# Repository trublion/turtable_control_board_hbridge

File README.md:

## Description

HW control board for turntable. Controls a DC motor with a H-bridge, reads an analog audio signal envelope, dual-PCB design.

## Links (datasheets and documentation)

[IEC plug](https://www.schurter.com/en/datasheet/typ_6765.pdf)  
[Potentiometer RK09L](https://tech.alpsalpine.com/prod/e/pdf/potentiometer/rotarypotentiometers/rk09l/rk09l.pdf)  
[Neutrik combo](https://www.neutrik.com/en/product/nj3fp6c.pdf)  
[74HCT4066](https://assets.nexperia.com/documents/data-sheet/74HC_HCT4066.pdf)  
[Shunt resistors](https://www.te.com/commerce/DocumentDelivery/DDEController?Action=showdoc&DocId=Data+Sheet%7F9-1773463-7%7FG%7Fpdf%7FEnglish%7FENG_DS_9-1773463-7_G.pdf%7FCAT-C339-A76B)  
[BAS21 small signal diode](https://www.vishay.com/docs/85540/bas19.pdf)  
[Zener diodes](https://assets.nexperia.com/documents/data-sheet/BZX84_SER.pdf)  
[Electrolytic capacitors](https://industrial.panasonic.com/cdbs/www-data/pdf/RDE0000/ABA0000C1181.pdf)  
[LM358 comparator](https://www.ti.com/lit/ds/symlink/lm158-n.pdf)  
[LM833 operational amplifier](https://www.ti.com/lit/ds/symlink/lm833-n.pdf)  
[LM2674 DCDC controller](https://www.ti.com/lit/ds/symlink/lm2674.pdf)  
[MBRS3100T3G Schottky power diode](https://www.onsemi.com/pdf/datasheet/mbrs3100t3-d.pdf)  
[RS2 power diode](https://www.semiee.com/file/ELMX/MULTICOMP-RS2A.pdf)  
[Power inductor](https://www.bourns.com/docs/Product-Datasheets/SRR0735A.pdf)

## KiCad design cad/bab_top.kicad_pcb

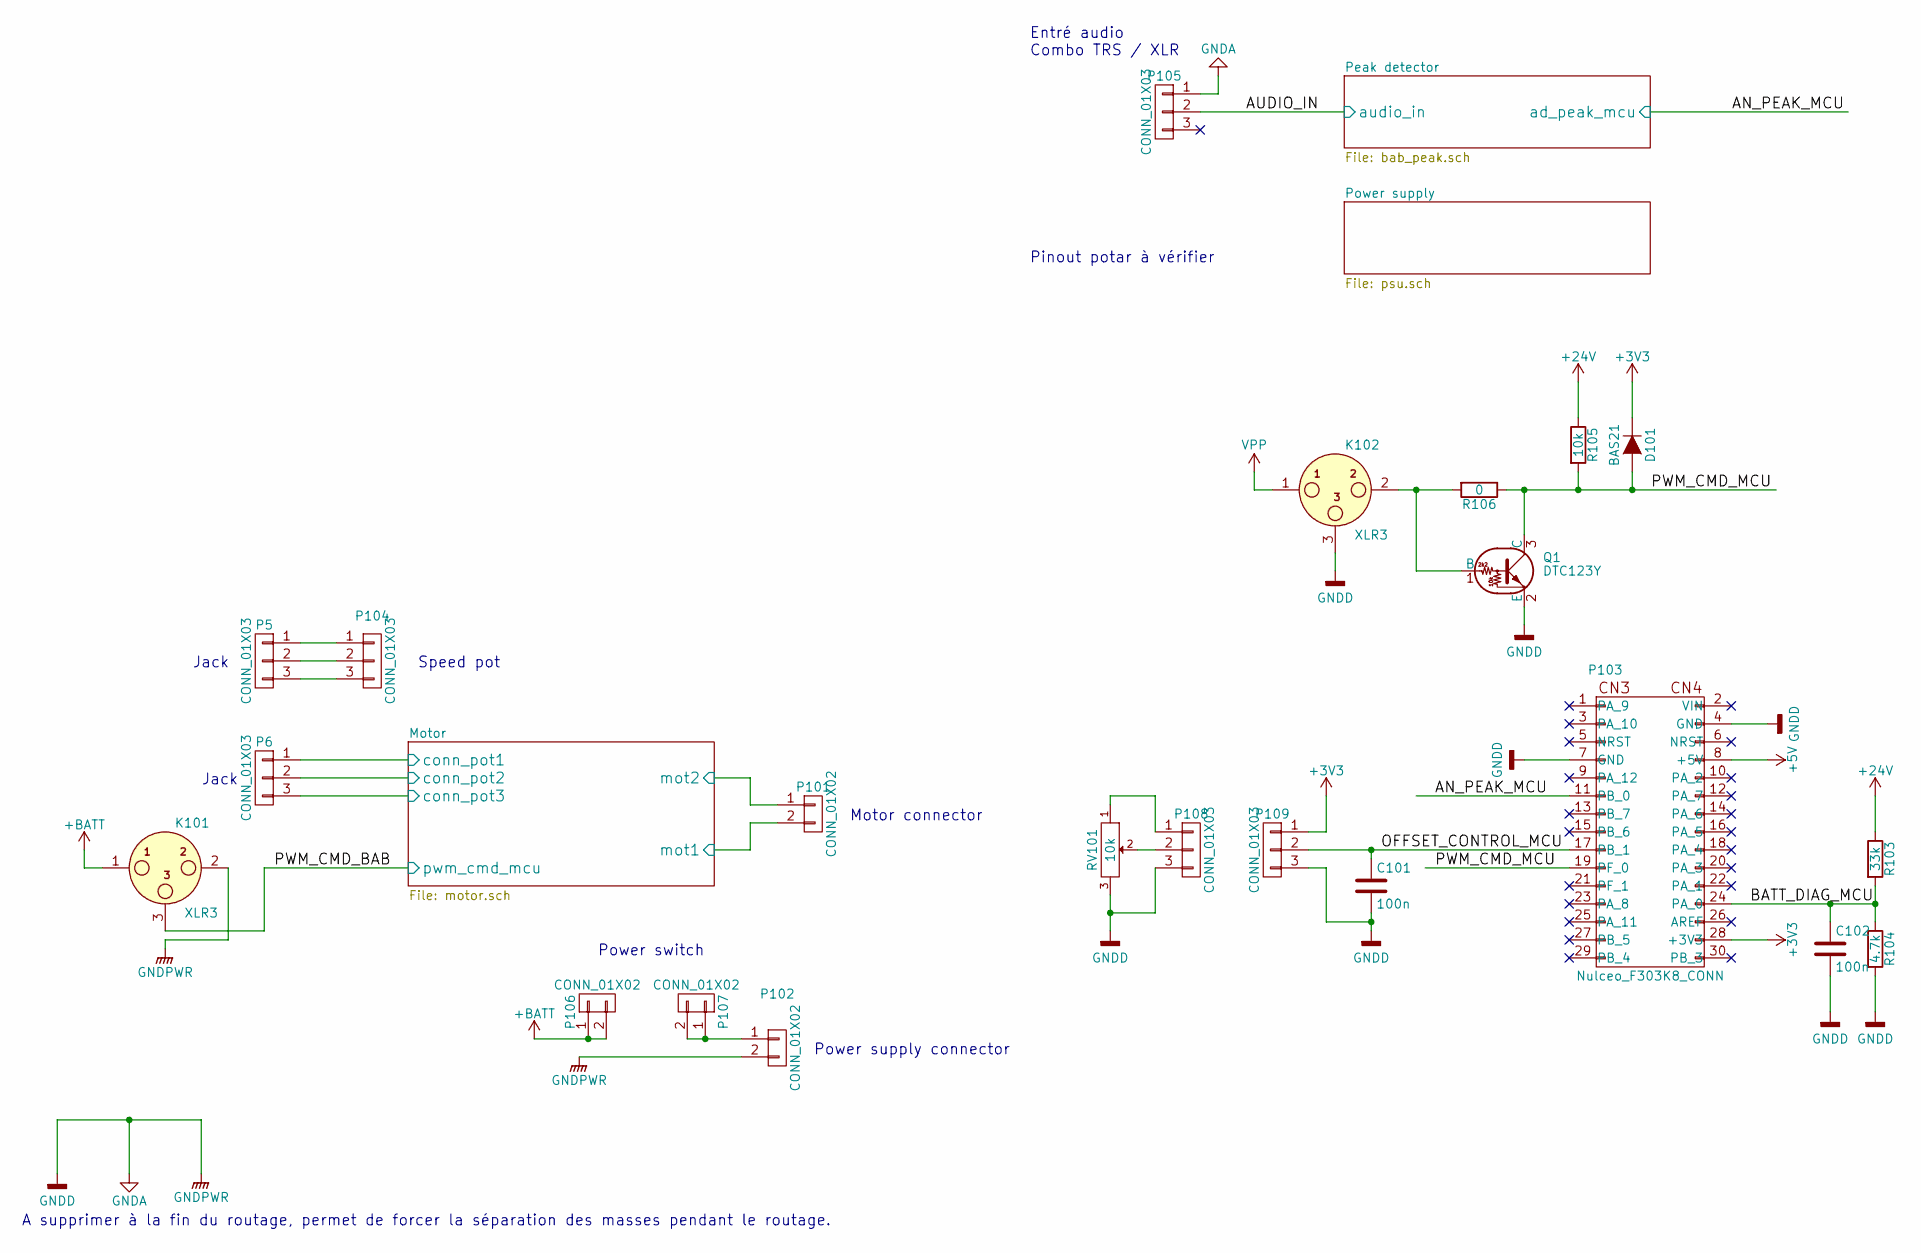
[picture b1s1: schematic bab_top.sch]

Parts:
C101, C102: 100n; C_0805_HandSoldering
D101: BAS21; SOT-23
K101, K102: XLR3; Pin_Header_Straight_1x03
P5, P6, P104, P105, P108, P109: CONN_01X03; Pin_Header_Straight_1x03
P101, P102, P106, P107: CONN_01X02; bornier2
P103: Nulceo_F303K8_CONN; Nucleo_F303K8_CONN
Q1: DTC123Y; SOT-23_Handsoldering
R103: 33k; C_0805_HandSoldering
R104: 4.7k; C_0805_HandSoldering
R105: 10k; C_0805_HandSoldering
R106: 0; C_0805_HandSoldering
RV101: 10k; Pin_Header_Straight_1x03

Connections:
+5V: P103.8 (+5V); also elsewhere on the board
+24V: R103.1, R105.1; also elsewhere on the board
+BATT: K101.1, P106.1, P106.2; also elsewhere on the board
/BATT_DIAG_MCU: C102.1, P103.24 (PA_0), R103.2, R104.1
/Motor/conn_pot1: P6.1; also elsewhere on the board
/Motor/conn_pot2: P6.2; also elsewhere on the board
/Motor/conn_pot3: P6.3; also elsewhere on the board
/Motor/mot1: P101.2; also elsewhere on the board
/Motor/mot2: P101.1; also elsewhere on the board
/Motor/pwm_cmd_mcu: K101.3; also elsewhere on the board
/OFFSET_CONTROL_MCU: C101.1, P103.17 (PB_1), P109.2
/PWM_CMD_MCU: D101.1 (A), P103.19 (PF_0), Q1.3 (C), R105.2, R106.1
/Peak detector/ad_peak_mcu: P103.11 (PB_0); also elsewhere on the board
/Peak detector/audio_in: P105.2; also elsewhere on the board
GND: C101.2, C102.2, K101.2, K102.3, P102.2, P103.4 (GND), P103.7 (GND), P105.1, P108.3, P109.3, Q1.2 (E), R104.2, RV101.3; also elsewhere on the board
unnamed: K102.2, Q1.1 (B), R106.2
unnamed: P102.1, P107.1, P107.2
unnamed: P5.1, P104.1
unnamed: P5.2, P104.2
unnamed: P5.3, P104.3
unnamed: P108.1, RV101.1
unnamed: P108.2, RV101.2
VPP: K102.1; also elsewhere on the board

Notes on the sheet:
A supprimer à la fin du routage, permet de forcer la séparation des masses pendant le routage.
Pinout potar à vérifier
Entré audio Combo TRS / XLR
Power switch
Jack
Speed pot
Power supply connector
Motor connector

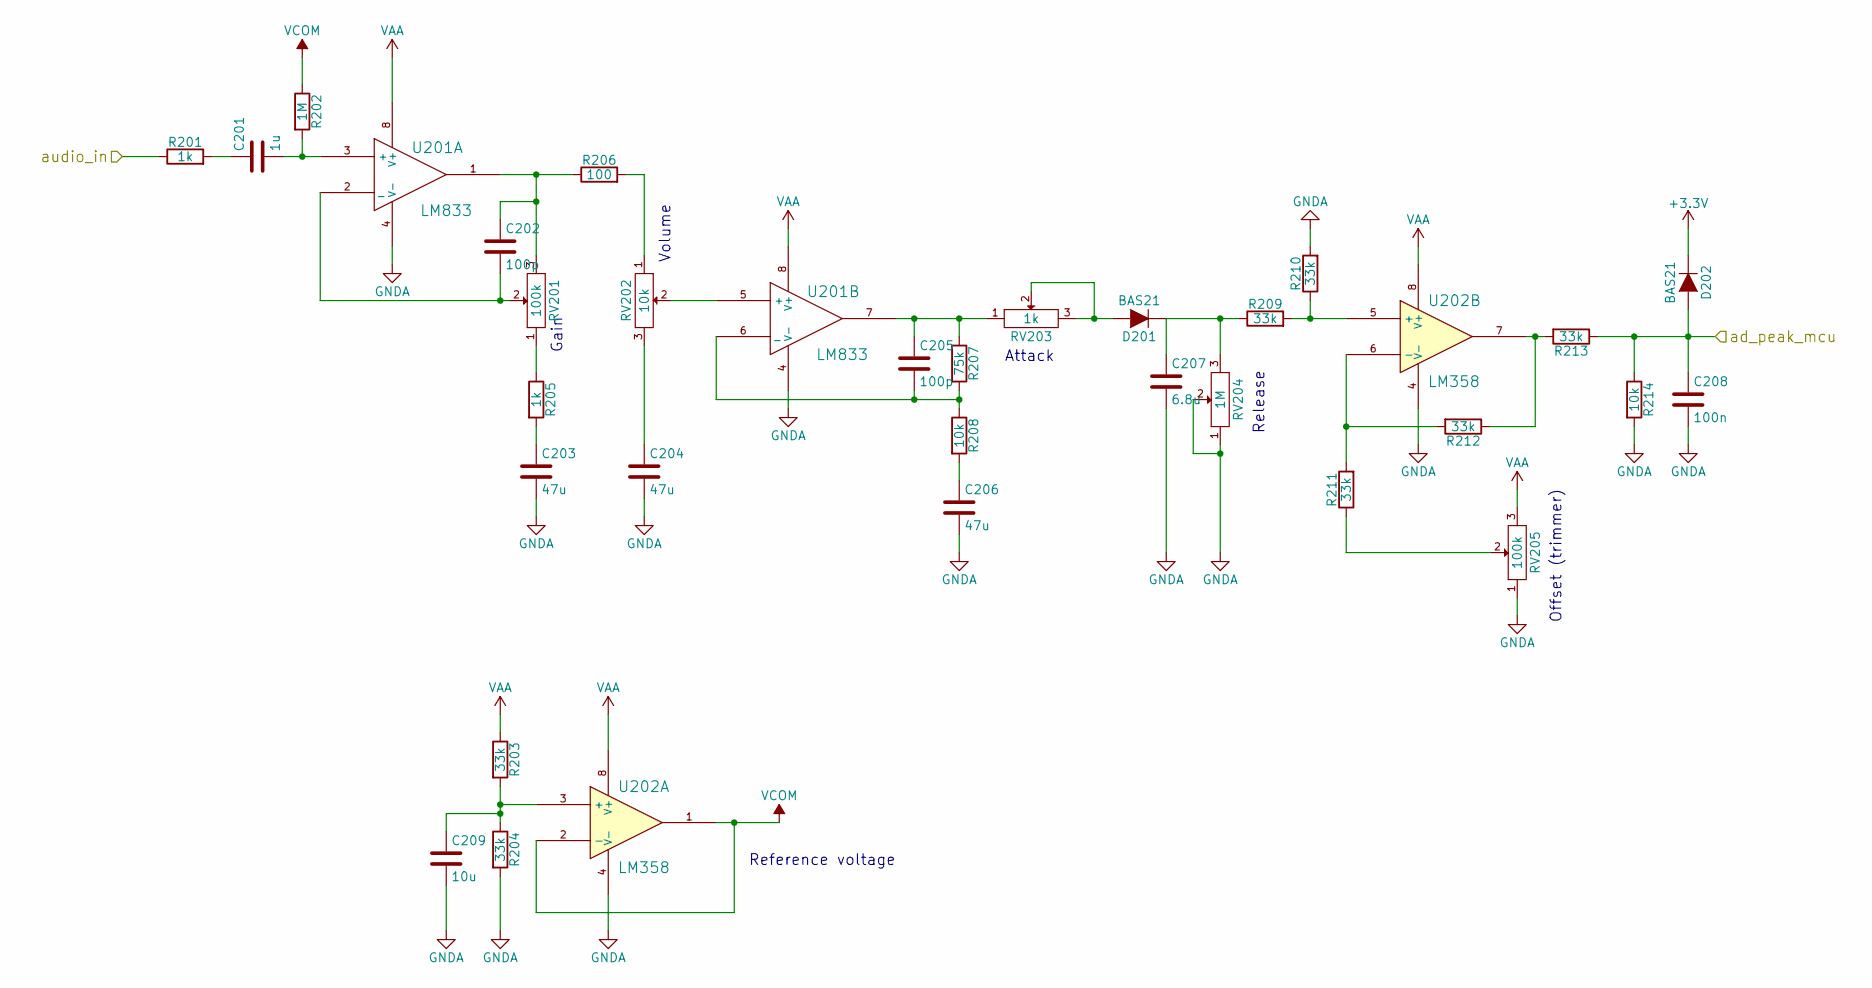
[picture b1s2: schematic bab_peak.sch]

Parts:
C201: 1u; C_2220_HandSoldering
C202, C205: 100p; C_0805_HandSoldering
C203, C204, C206: 47u; c_elec_6.3x5.8
C207: 6.8u; c_elec_5x5.7
C208: 100n; C_0805_HandSoldering
C209: 10u; c_elec_6.3x5.8
D201, D202: BAS21; SOT-23
R201, R205: 1k; C_0805_HandSoldering
R202: 1M; C_0805_HandSoldering
R203, R204, R209, R210, R211, R212, R213: 33k; C_0805_HandSoldering
R206: 100; C_0805_HandSoldering
R207: 75k; C_0805_HandSoldering
R208, R214: 10k; C_0805_HandSoldering
RV201, RV205: 100k; Pin_Header_Straight_1x03
RV202: 10k; Pin_Header_Straight_1x03
RV203: 1k; Pin_Header_Straight_1x03
RV204: 1M; Pin_Header_Straight_1x03
U201: LM833; SOIC-8_3.9x4.9mm_Pitch1.27mm
U202: LM358; SOIC-8_3.9x4.9mm_Pitch1.27mm

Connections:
/Peak detector/ad_peak_mcu: C208.1, D202.1 (A), R213.1, R214.1; also elsewhere on the board
/Peak detector/audio_in: R201.1; also elsewhere on the board
GND: C203.2, C204.2, C206.2, C207.2, C208.2, C209.2, R204.2, R210.2, R214.2, RV204.1, RV204.2, RV205.1, U201.4 (V-), U202.4 (V-); also elsewhere on the board
unnamed: C201.1, R201.2
unnamed: C201.2, R202.2, U201.3 (+)
unnamed: C202.1, R206.1, RV201.3, U201.1
unnamed: C202.2, RV201.2, U201.2 (_)
unnamed: C203.1, R205.2
unnamed: C204.1, RV202.3
unnamed: C205.1, R207.1, RV203.1, U201.7
unnamed: C205.2, R207.2, R208.1, U201.6 (_)
unnamed: C206.1, R208.2
unnamed: C207.1, D201.3 (K), R209.1, RV204.3
unnamed: C209.1, R203.2, R204.1, U202.3 (+)
unnamed: D201.1 (A), RV203.2, RV203.3
unnamed: R205.1, RV201.1
unnamed: R206.2, RV202.1
unnamed: R209.2, R210.1, U202.5 (+)
unnamed: R211.1, RV205.2
unnamed: R211.2, R212.2, U202.6 (-)
unnamed: R212.1, R213.2, U202.7
unnamed: RV202.2, U201.5 (+)
VAA: R203.1, RV205.3, U201.8 (V+), U202.8 (V+); also elsewhere on the board
VCOM: R202.1, U202.1, U202.2 (-)

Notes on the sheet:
Offset (trimmer)
Release
Attack
Gain
Volume
Reference voltage

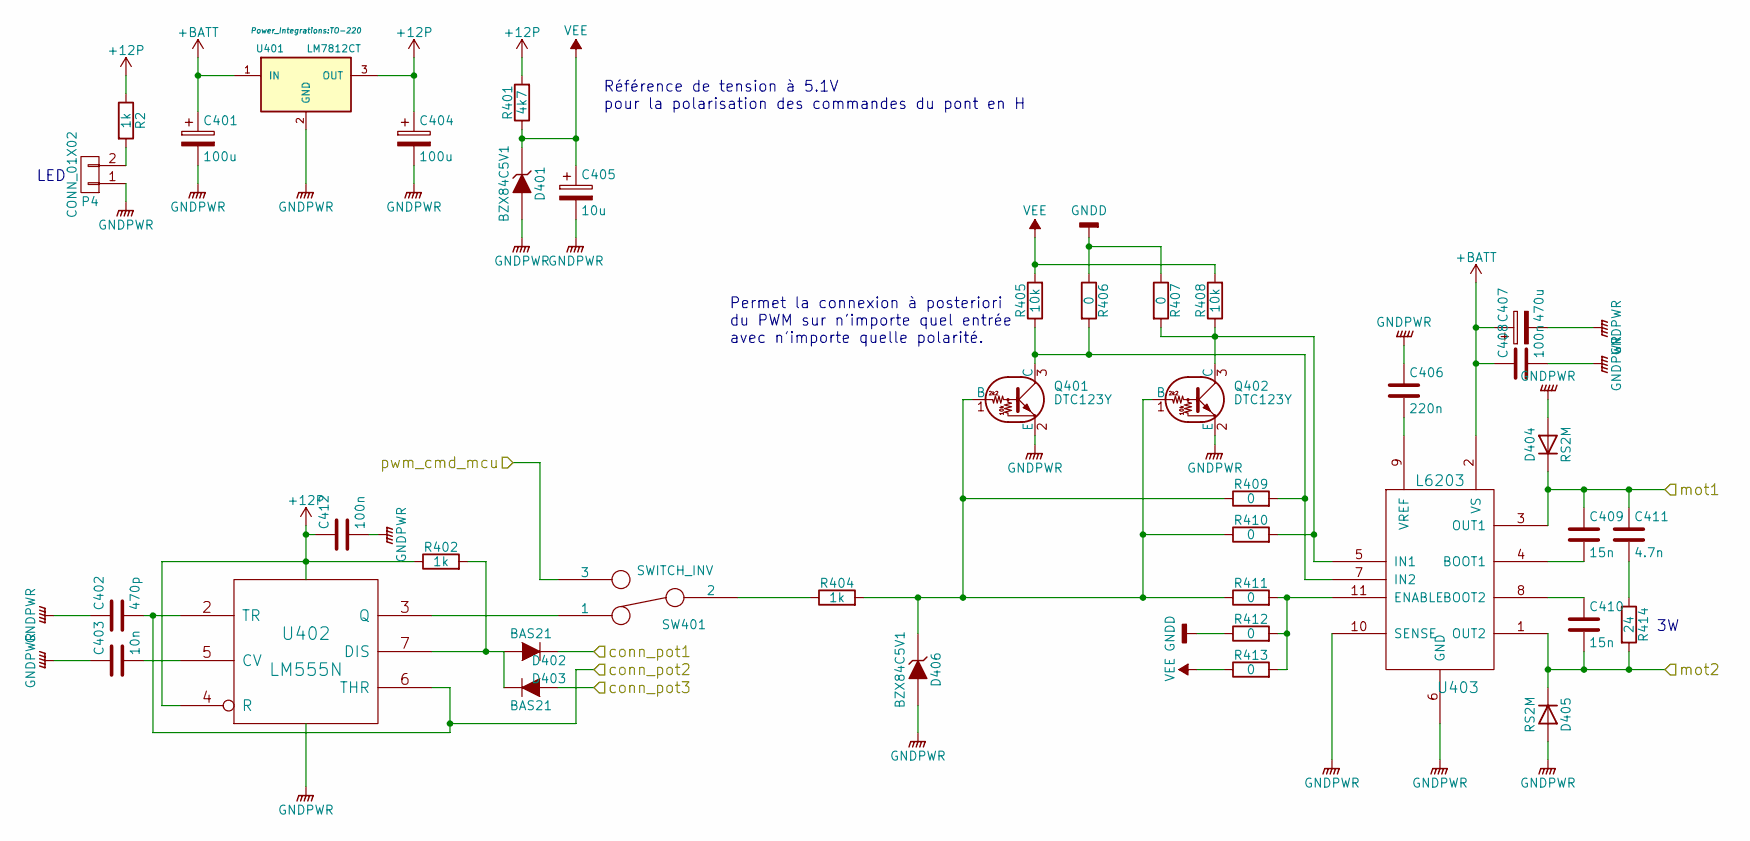
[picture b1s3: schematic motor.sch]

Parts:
C401, C404: 100u; c_elec_6.3x7.7
C402: 470p; C_0805_HandSoldering
C403: 10n; C_0805_HandSoldering
C405: 10u; c_elec_6.3x5.8
C406: 220n; C_0805_HandSoldering
C407: 470u; c_elec_16x16.8
C408, C412: 100n; C_0805_HandSoldering
C409, C410: 15n; C_0805_HandSoldering
C411: 4.7n; C_0805_HandSoldering
D401, D406: BZX84C5V1; SOT-23
D402, D403: BAS21; SOT-23
D404, D405: RS2M; DO-214AA_Handsoldering
P4: CONN_01X02; Pin_Header_Straight_1x02
Q401, Q402: DTC123Y; SOT-23
R2: 1k; R_0805_HandSoldering
R401: 4k7; C_0805_HandSoldering
R402, R404: 1k; C_0805_HandSoldering
R405, R408: 10k; C_0805_HandSoldering
R406, R407, R409, R410, R411, R412, R413: 0; C_0805_HandSoldering
R414: 24; C_3522_HandSoldering
SW401: SWITCH_INV; Pin_Header_Straight_1x03
U401: LM7812CT; TO-220
U402: LM555N; SOIC-8_3.9x4.9mm_Pitch1.27mm
U403: L6203; Multiwatt_11_Vertical

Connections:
+12P: C404.1, C412.1, R2.1, R401.2, R402.1, U401.3 (OUT), U402.4 (R), U402.8 (VCC)
+BATT: C401.1, C407.1, C408.1, U401.1 (IN), U403.2 (VS); also elsewhere on the board
/Motor/conn_pot1: D402.3 (K); also elsewhere on the board
/Motor/conn_pot2: C402.2, U402.2 (TR), U402.6 (THR); also elsewhere on the board
/Motor/conn_pot3: D403.1 (A); also elsewhere on the board
/Motor/mot1: C409.1, C411.1, D404.1 (K), U403.3 (OUT1); also elsewhere on the board
/Motor/mot2: C410.2, D405.1 (K), R414.2, U403.1 (OUT2); also elsewhere on the board
/Motor/pwm_cmd_mcu: SW401.3; also elsewhere on the board
GND: C401.2, C402.1, C403.1, C404.2, C405.2, C406.1, C407.2, C408.2, C412.2, D401.1 (A), D404.2 (A), D405.2 (A), D406.1 (A), P4.1, Q401.2 (E), Q402.2 (E), R406.1, R407.1, R412.1, U401.2 (GND), U402.1 (GND), U403.6 (GND), U403.10 (SENSE); also elsewhere on the board
unnamed: C403.2, U402.5 (CV)
unnamed: C406.2, U403.9 (VREF)
unnamed: C409.2, U403.4 (BOOT1)
unnamed: C410.1, U403.8 (BOOT2)
unnamed: C411.2, R414.1
unnamed: D402.1 (A), D403.3 (K), R402.2, U402.7 (DIS)
unnamed: D406.3 (K), Q401.1 (B), Q402.1 (B), R404.2, R409.1, R410.1, R411.1
unnamed: P4.2, R2.2
unnamed: Q401.3 (C), R405.1, R406.2, R409.2, U403.7 (IN2)
unnamed: Q402.3 (C), R407.2, R408.1, R410.2, U403.5 (IN1)
unnamed: R404.1, SW401.2
unnamed: R411.2, R412.2, R413.2, U403.11 (ENABLE)
unnamed: SW401.1, U402.3 (Q)
VEE: C405.1, D401.3 (K), R401.1, R405.2, R408.2, R413.1

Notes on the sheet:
Référence de tension à 5.1V pour la polarisation des commandes du pont en H
Permet la connexion à posteriori du PWM sur n'importe quel entrée avec n'importe quelle polarité.
LED

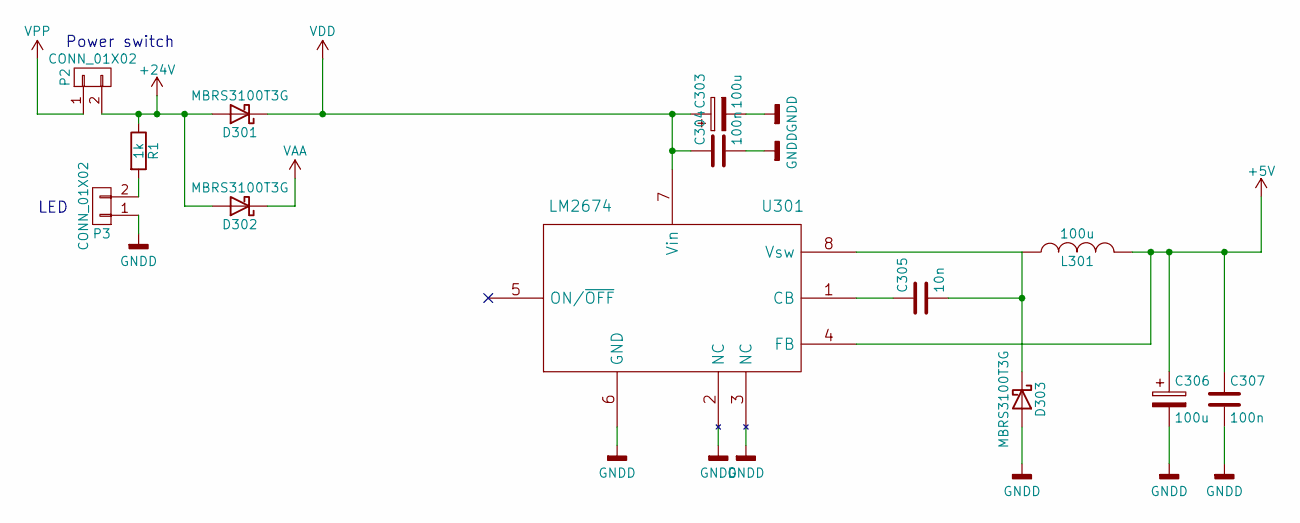
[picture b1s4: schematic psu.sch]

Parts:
C303, C306: 100u; c_elec_6.3x7.7
C304, C307: 100n; C_0805_HandSoldering
C305: 10n; C_0805_HandSoldering
D301, D302, D303: MBRS3100T3G; DO-214AB
L301: 100u; Choke_SMD_7.3x7.3_H3.5
P2, P3: CONN_01X02; Pin_Header_Straight_1x02
R1: 1k; R_0805_HandSoldering
U301: LM2674; SOIC-8_3.9x4.9mm_Pitch1.27mm

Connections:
+5V: C306.1, C307.1, L301.2, U301.4 (FB); also elsewhere on the board
+24V: D301.2 (A), D302.2 (A), P2.2, R1.1; also elsewhere on the board
GND: C303.2, C304.2, C306.2, C307.2, D303.2 (A), P3.1, U301.2 (NC), U301.3 (NC), U301.6 (GND); also elsewhere on the board
unnamed: C305.1, U301.1 (CB)
unnamed: C305.2, D303.1 (K), L301.1, U301.8 (Vsw)
unnamed: P3.2, R1.2
VAA: D302.1 (K); also elsewhere on the board
VDD: C303.1, C304.1, D301.1 (K), U301.7 (Vin)
VPP: P2.1; also elsewhere on the board

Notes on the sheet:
Power switch
LED

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
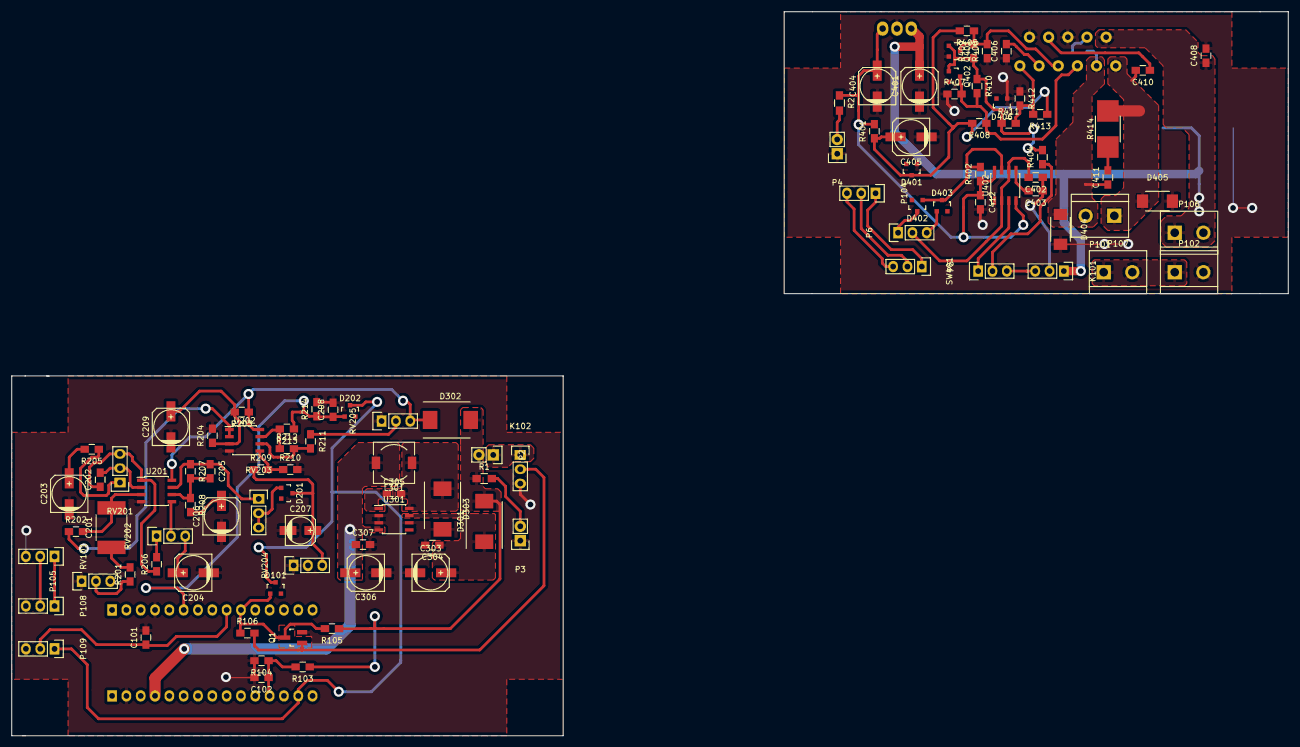
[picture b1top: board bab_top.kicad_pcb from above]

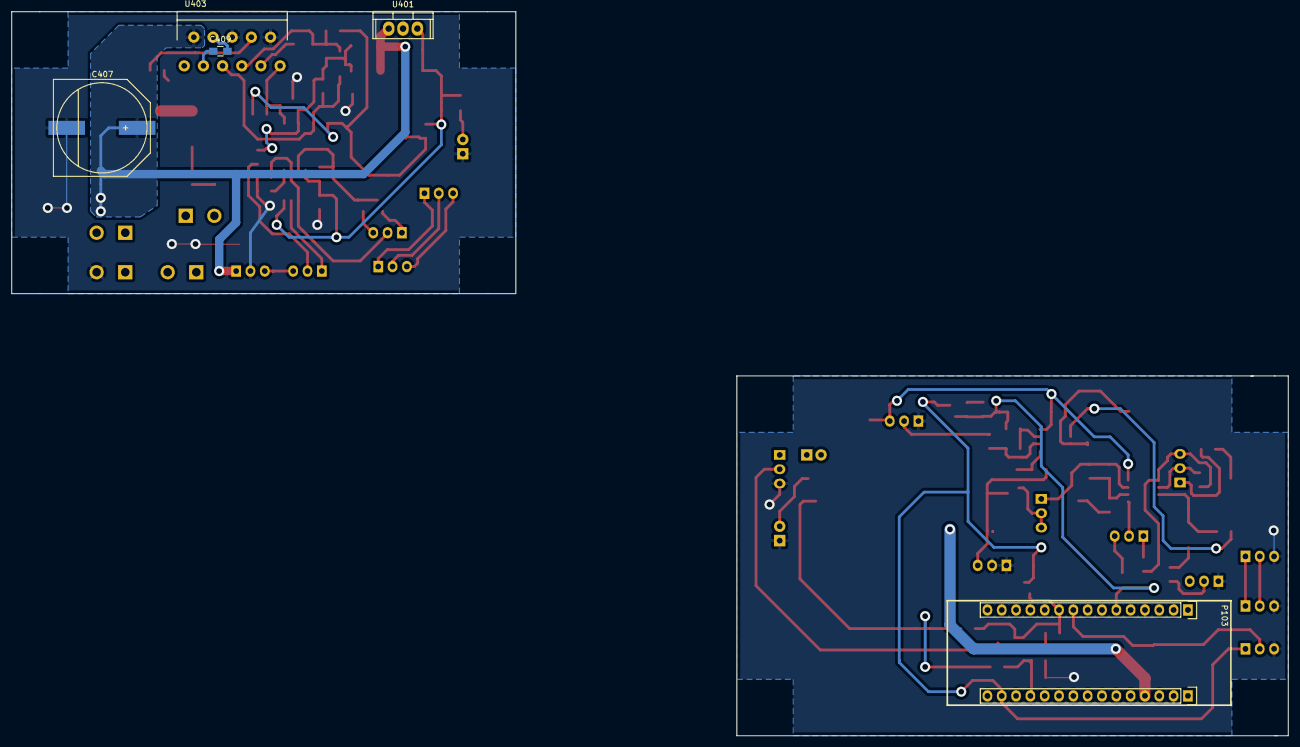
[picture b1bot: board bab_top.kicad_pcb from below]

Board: 2 copper layers, 226.4 x 128.4 mm, 106 parts (5 on the bottom side), 64 nets.

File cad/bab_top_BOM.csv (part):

"Source:","C:\Users\Florian\Documents\dev\trublion\bab leo maurel\v2\cad\bab_top.sch"
"Date:","11/04/2021 16:08:11"
"Tool:","Eeschema (5.1.9)-1"
"Generator:","E:\dev\KiCad\bin\scripting\plugins/bom_csv_grouped_by_value.py"
"Component Count:","106"

"Individual Components:"

"Item","Qty","Reference(s)","Value","LibPart","Footprint","Datasheet"
"","","C101","100n","Device:C","Capacitors_SMD:C_0805_HandSoldering",""
"","","C102","100n","Device:C","Capacitors_SMD:C_0805_HandSoldering",""
"","","C201","1u","Device:C","Capacitors_SMD:C_2220_HandSoldering",""
"","","C202","100p","Device:C","Capacitors_SMD:C_0805_HandSoldering",""
"","","C203","47u","Device:C","Capacitors_SMD:c_elec_6.3x5.8",""
"","","C204","47u","Device:C","Capacitors_SMD:c_elec_6.3x5.8",""
"","","C205","100p","Device:C","Capacitors_SMD:C_0805_HandSoldering",""
"","","C206","47u","Device:C","Capacitors_SMD:c_elec_6.3x5.8",""
"","","C207","6.8u","Device:C","Capacitors_SMD:c_elec_5x5.7",""
"","","C208","100n","Device:C","Capacitors_SMD:C_0805_HandSoldering",""
"","","C209","10u","Device:C","Capacitors_SMD:c_elec_6.3x5.8",""
"","","C303","100u","Device:CP","Capacitors_SMD:c_elec_6.3x7.7",""
"","","C304","100n","Device:C","Capacitors_SMD:C_0805_HandSoldering",""
"","","C305","10n","Device:C","Capacitors_SMD:C_0805_HandSoldering",""
"","","C306","100u","Device:CP","Capacitors_SMD:c_elec_6.3x7.7",""
"","","C307","100n","Device:C","Capacitors_SMD:C_0805_HandSoldering",""
"","","C401","100u","Device:CP","Capacitors_SMD:c_elec_6.3x7.7",""
"","","C402","470p","Device:C","Capacitors_SMD:C_0805_HandSoldering",""
"","","C403","10n","Device:C","Capacitors_SMD:C_0805_HandSoldering",""
"","","C404","100u","Device:CP","Capacitors_SMD:c_elec_6.3x7.7",""
"","","C405","10u","Device:CP","Capacitors_SMD:c_elec_6.3x5.8",""
"","","C406","220n","Device:C","Capacitors_SMD:C_0805_HandSoldering",""
"","","C407","470u","Device:CP","bab_footprint:c_elec_16x16.8",""
"","","C408","100n","Device:C","Capacitors_SMD:C_0805_HandSoldering",""
"","","C409","15n","Device:C","Capacitors_SMD:C_0805_HandSoldering",""
"","","C410","15n","Device:C","Capacitors_SMD:C_0805_HandSoldering",""
"","","C411","4.7n","Device:C","Capacitors_SMD:C_0805_HandSoldering",""
"","","C412","100n","Device:C","Capacitors_SMD:C_0805_HandSoldering",""
"","","D101","BAS21","bab:BAS21","TO_SOT_Packages_SMD:SOT-23",""
"","","D201","BAS21","bab:BAS21","TO_SOT_Packages_SMD:SOT-23",""
"","","D202","BAS21","bab:BAS21","TO_SOT_Packages_SMD:SOT-23",""
"","","D301","MBRS3100T3G","Device:D_Schottky","Diodes_SMD:DO-214AB",""
"","","D302","MBRS3100T3G","Device:D_Schottky","Diodes_SMD:DO-214AB",""
"","","D303","MBRS3100T3G","Device:D_Schottky","Diodes_SMD:DO-214AB",""
"","","D401","BZX84C5V1","bab:BZX84C5V1","TO_SOT_Packages_SMD:SOT-23",""
"","","D402","BAS21","bab:BAS21","TO_SOT_Packages_SMD:SOT-23",""
"","","D403","BAS21","bab:BAS21","TO_SOT_Packages_SMD:SOT-23",""
"","","D404","RS2M","Device:D","bab_footprint:DO-214AA_Handsoldering",""
"","","D405","RS2M","Device:D","bab_footprint:DO-214AA_Handsoldering",""
"","","D406","BZX84C5V1","bab:BZX84C5V1","TO_SOT_Packages_SMD:SOT-23",""
"","","K101","XLR3","bab_top-rescue:XLR3","Pin_Headers:Pin_Header_Straight_1x03",""
"","","K102","XLR3","bab_top-rescue:XLR3","Pin_Headers:Pin_Header_Straight_1x03",""
"","","L301","100u","bab_top-rescue:INDUCTOR","Choke_SMD:Choke_SMD_7.3x7.3_H3.5",""
"","","P2","CONN_01X02","bab_top-rescue:CONN_01X02","Pin_Headers:Pin_Header_Straight_1x02",""
"","","P3","CONN_01X02","bab_top-rescue:CONN_01X02","Pin_Headers:Pin_Header_Straight_1x02",""
"","","P4","CONN_01X02","bab_top-rescue:CONN_01X02","Pin_Headers:Pin_Header_Straight_1x02",""
"","","P5","CONN_01X03","bab_top-rescue:CONN_01X03","Pin_Headers:Pin_Header_Straight_1x03",""
"","","P6","CONN_01X03","bab_top-rescue:CONN_01X03","Pin_Headers:Pin_Header_Straight_1x03",""
"","","P101","CONN_01X02","bab_top-rescue:CONN_01X02","Connect:bornier2",""
"","","P102","CONN_01X02","bab_top-rescue:CONN_01X02","Connect:bornier2",""
"","","P103","Nulceo_F303K8_CONN","bab:Nulceo_F303K8_CONN","bab_footprint:Nucleo_F303K8_CONN",""
"","","P104","CONN_01X03","bab_top-rescue:CONN_01X03","Pin_Headers:Pin_Header_Straight_1x03",""
"","","P105","CONN_01X03","bab_top-rescue:CONN_01X03","Pin_Headers:Pin_Header_Straight_1x03",""
"","","P106","CONN_01X02","bab_top-rescue:CONN_01X02","Connect:bornier2",""
"","","P107","CONN_01X02","bab_top-rescue:CONN_01X02","Connect:bornier2",""
"","","P108","CONN_01X03","bab_top-rescue:CONN_01X03","Pin_Headers:Pin_Header_Straight_1x03",""
"","","P109","CONN_01X03","bab_top-rescue:CONN_01X03","Pin_Headers:Pin_Header_Straight_1x03",""
"","","Q1","DTC123Y","bab_top-rescue:DTC123Y","TO_SOT_Packages_SMD:SOT-23_Handsoldering",""
"","","Q401","DTC123Y","bab_top-rescue:DTC123Y","TO_SOT_Packages_SMD:SOT-23",""
"","","Q402","DTC123Y","bab_top-rescue:DTC123Y","TO_SOT_Packages_SMD:SOT-23",""
"","","R1","1k","Device:R","Resistors_SMD:R_0805_HandSoldering",""
"","","R2","1k","Device:R","Resistors_SMD:R_0805_HandSoldering",""
"","","R103","33k","Device:R","Capacitors_SMD:C_0805_HandSoldering",""
"","","R104","4.7k","Device:R","Capacitors_SMD:C_0805_HandSoldering",""
"","","R105","10k","Device:R","Capacitors_SMD:C_0805_HandSoldering",""
"","","R106","0","Device:R","Capacitors_SMD:C_0805_HandSoldering",""
"","","R201","1k","Device:R","Capacitors_SMD:C_0805_HandSoldering",""
"","","R202","1M","Device:R","Capacitors_SMD:C_0805_HandSoldering",""
"","","R203","33k","Device:R","Capacitors_SMD:C_0805_HandSoldering",""
"","","R204","33k","Device:R","Capacitors_SMD:C_0805_HandSoldering",""
"","","R205","1k","Device:R","Capacitors_SMD:C_0805_HandSoldering",""
"","","R206","100","Device:R","Capacitors_SMD:C_0805_HandSoldering",""
"","","R207","75k","Device:R","Capacitors_SMD:C_0805_HandSoldering",""
"","","R208","10k","Device:R","Capacitors_SMD:C_0805_HandSoldering",""
"","","R209","33k","Device:R","Capacitors_SMD:C_0805_HandSoldering",""
"","","R210","33k","Device:R","Capacitors_SMD:C_0805_HandSoldering",""
"","","R211","33k","Device:R","Capacitors_SMD:C_0805_HandSoldering",""
"","","R212","33k","Device:R","Capacitors_SMD:C_0805_HandSoldering",""
"","","R213","33k","Device:R","Capacitors_SMD:C_0805_HandSoldering",""
"","","R214","10k","Device:R","Capacitors_SMD:C_0805_HandSoldering",""
"","","R401","4k7","Device:R","Capacitors_SMD:C_0805_HandSoldering",""
"","","R402","1k","Device:R","Capacitors_SMD:C_0805_HandSoldering",""
"","","R404","1k","Device:R","Capacitors_SMD:C_0805_HandSoldering",""
"","","R405","10k","Device:R","Capacitors_SMD:C_0805_HandSoldering",""
"","","R406","0","Device:R","Capacitors_SMD:C_0805_HandSoldering",""
"","","R407","0","Device:R","Capacitors_SMD:C_0805_HandSoldering",""
"","","R408","10k","Device:R","Capacitors_SMD:C_0805_HandSoldering",""
"","","R409","0","Device:R","Capacitors_SMD:C_0805_HandSoldering",""
"","","R410","0","Device:R","Capacitors_SMD:C_0805_HandSoldering",""
"","","R411","0","Device:R","Capacitors_SMD:C_0805_HandSoldering",""
"","","R412","0","Device:R","Capacitors_SMD:C_0805_HandSoldering",""
"","","R413","0","Device:R","Capacitors_SMD:C_0805_HandSoldering",""
"","","R414","24","Device:R","bab_footprint:C_3522_HandSoldering",""
"","","RV101","10k","bab_top-rescue:POT","Pin_Headers:Pin_Header_Straight_1x03",""
"","","RV201","100k","bab_top-rescue:POT","Pin_Headers:Pin_Header_Straight_1x03",""
"","","RV202","10k","bab_top-rescue:POT","Pin_Headers:Pin_Header_Straight_1x03",""
"","","RV203","1k","bab_top-rescue:POT","Pin_Headers:Pin_Header_Straight_1x03",""
"","","RV204","1M","bab_top-rescue:POT","Pin_Headers:Pin_Header_Straight_1x03",""
"","","RV205","100k","bab_top-rescue:POT","Pin_Headers:Pin_Header_Straight_1x03",""
"","","SW401","SWITCH_INV","bab_top-rescue:SWITCH_INV","Pin_Headers:Pin_Header_Straight_1x03",""
"","","U201","LM833","bab:LM833","Housings_SOIC:SOIC-8_3.9x4.9mm_Pitch1.27mm",""
"","","U202","LM358","bab_top-rescue:LM358-RESCUE-bab_top","Housings_SOIC:SOIC-8_3.9x4.9mm_Pitch1.27mm",""
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
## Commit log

2021-04-11 Initial commit.
